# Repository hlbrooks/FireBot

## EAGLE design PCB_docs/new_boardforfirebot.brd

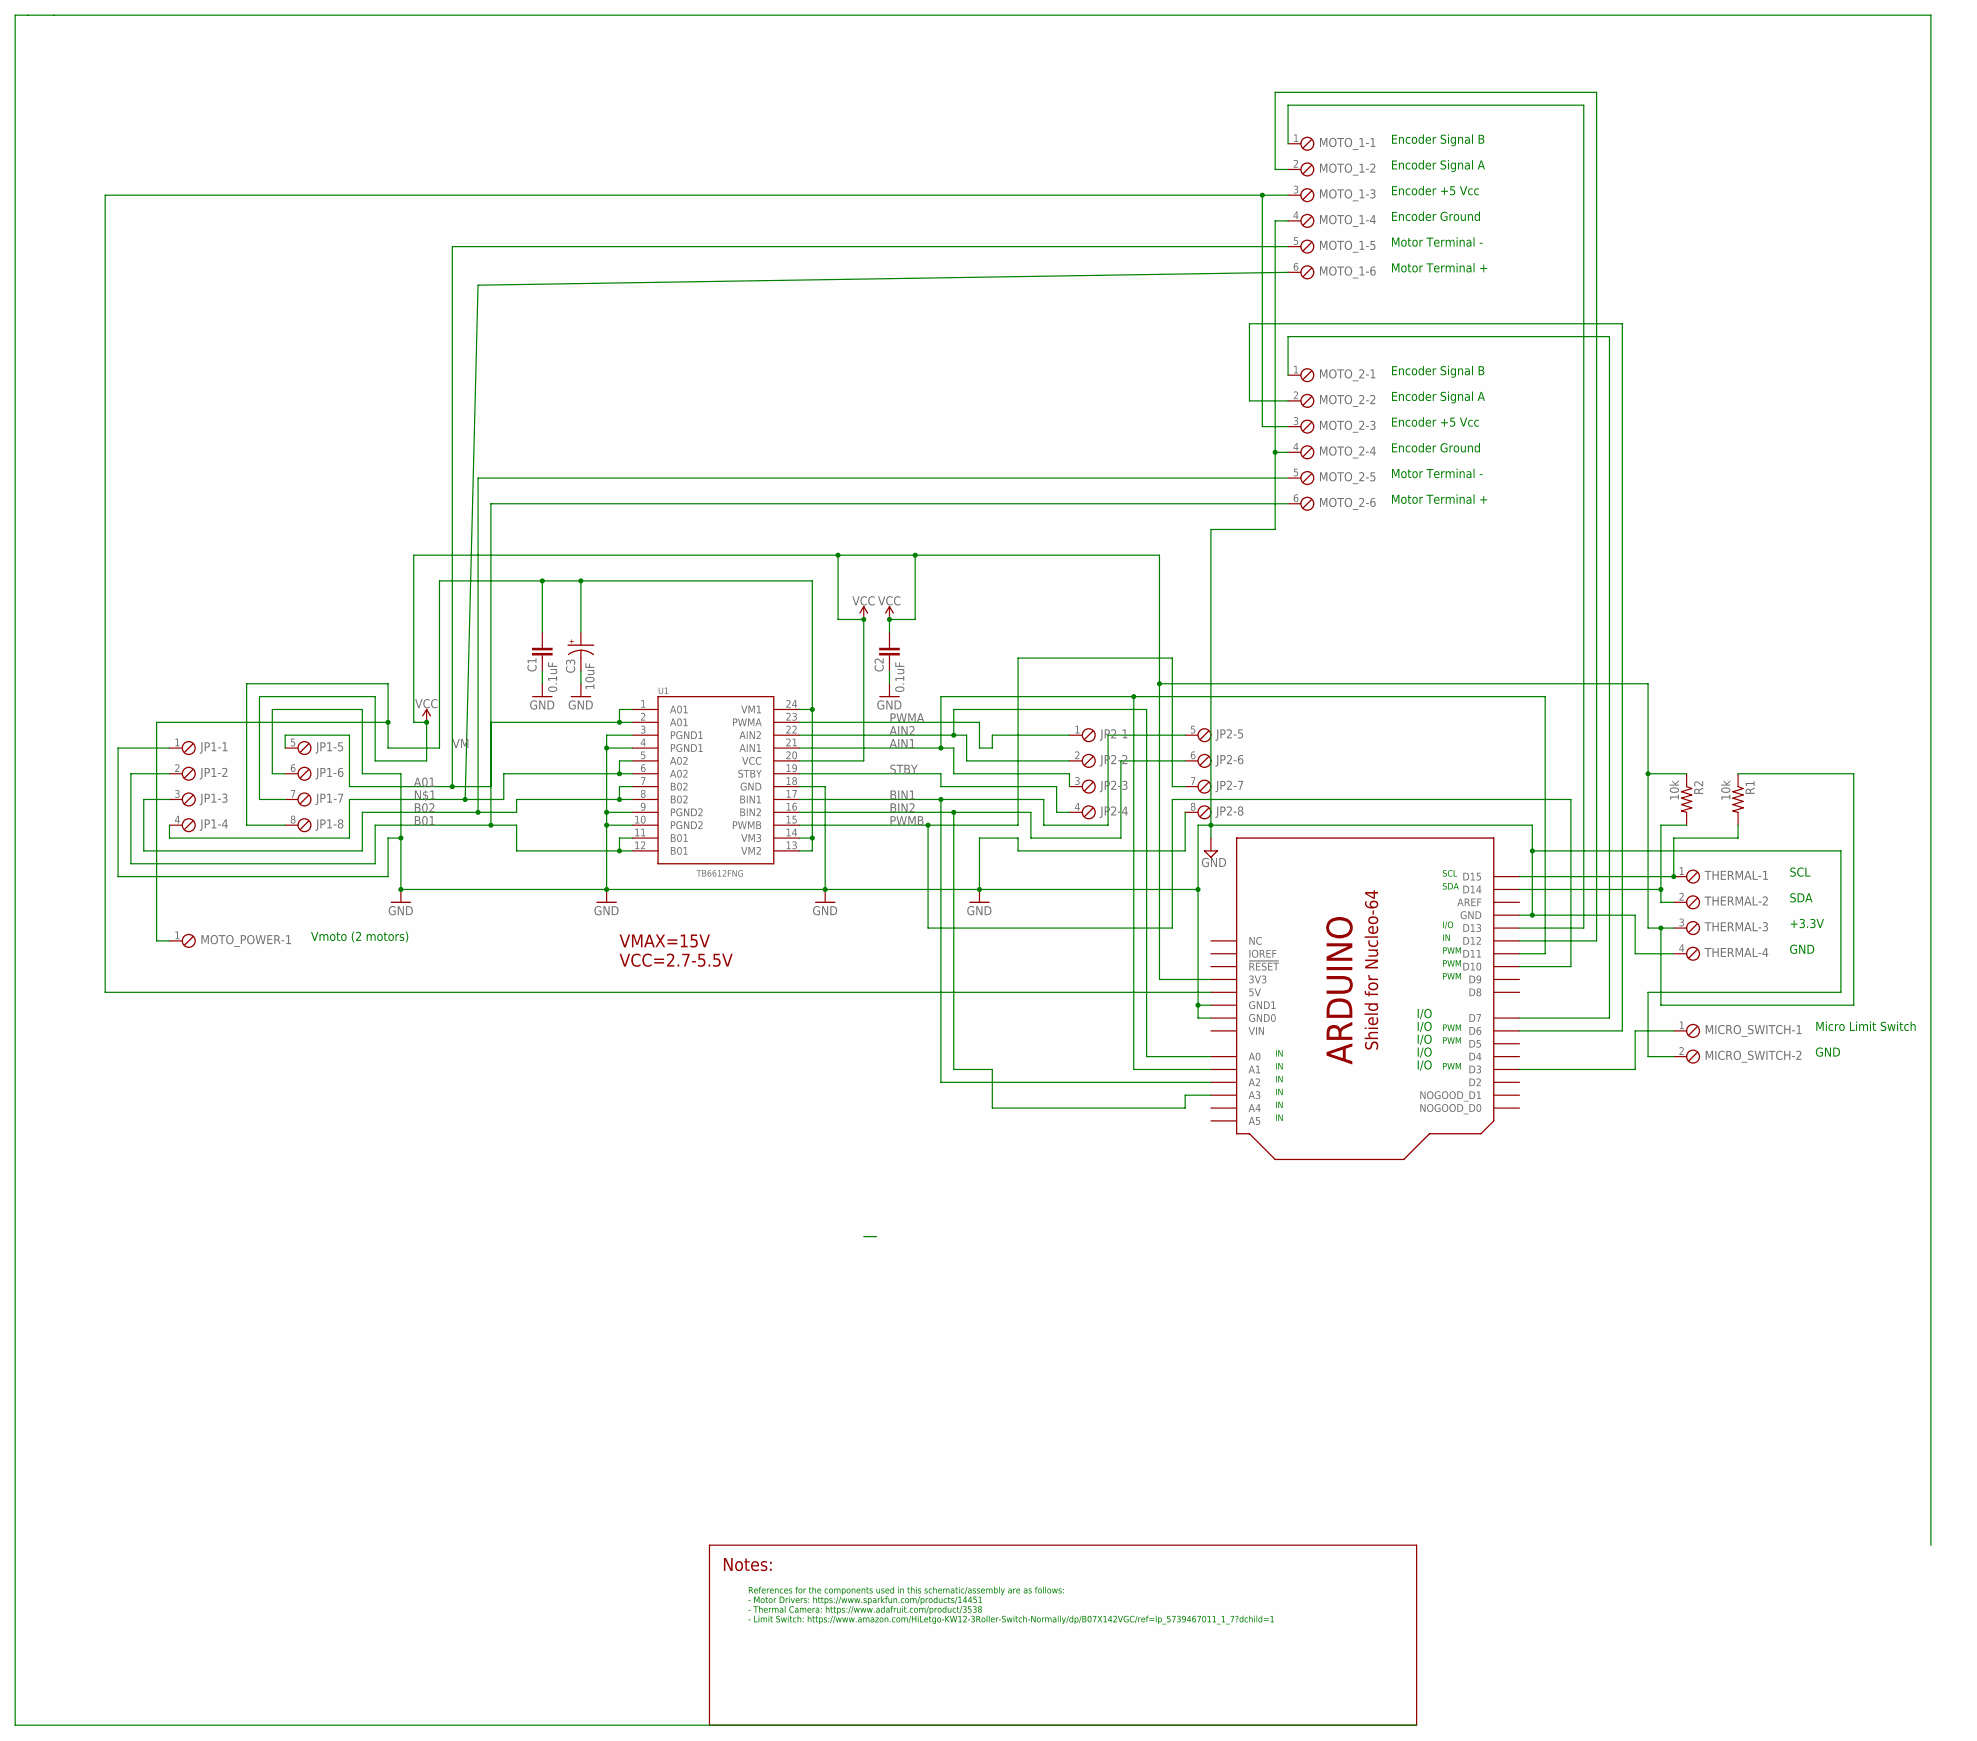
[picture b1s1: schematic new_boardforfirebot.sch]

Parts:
C1, C2: 0.1uF; 0402
C3: 10uF; EIA3528
JP1, JP2: SCREWTERM_8P_254; 8POL254
MICRO_SWITCH: SCREWTERM_2P_254; 2POL254
MOTO_1, MOTO_2: SCREWTERM_6P_254; 6POL254
MOTO_POWER: SCREWTERM_2P_254; 2POL254
R1, R2: 10k; R0805
THERMAL: SCREWTERM_4P_254; 4POL254
U1: TB6612FNG; SSOP24
U$1: SHIELD_FOR_NUCLE0_64_STANDARD; SHIELD_FOR_NUCLEO_64_STD

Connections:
A01: JP1.5, MOTO_1.5, U1.1 (A01), U1.2 (A01)
AIN1: JP2.3, U1.21 (AIN1), U$1.A1, U$1.D11
AIN2: JP2.2, U1.22 (AIN2), U$1.A0
B01: JP1.2, MOTO_2.6, U1.11 (B01), U1.12 (B01)
B02: JP1.3, MOTO_2.5, U1.7 (B02), U1.8 (B02)
BIN1: JP2.5, U1.17 (BIN1), U$1.A2
BIN2: JP2.6, U1.16 (BIN2), U$1.A3
GND: C1.2, C2.2, C3.C (-), JP1.1, JP1.6, JP2.8, MICRO_SWITCH.2, MOTO_1.4, MOTO_2.4, THERMAL.4, U1.3 (PGND1), U1.4 (PGND1), U1.9 (PGND2), U1.10 (PGND2), U1.18 (GND), U$1.GND, U$1.GND1 (GND0), U$1.GND2 (GND1)
unnamed: JP1.4, MOTO_1.6, U1.5 (A02), U1.6 (A02)
unnamed: MOTO_1.3, MOTO_2.3, U$1.5V
unnamed: MOTO_1.1, U$1.D13
unnamed: MOTO_1.2, U$1.D12
unnamed: MOTO_2.1, U$1.D7
unnamed: MOTO_2.2, U$1.D6
unnamed: R1.2, THERMAL.1, U$1.D15
unnamed: MICRO_SWITCH.1, U$1.D3
unnamed: R2.2, THERMAL.2, U$1.D14
PWMA: JP2.1, U1.23 (PWMA)
PWMB: JP2.7, U1.15 (PWMB), U$1.D10
STBY: JP2.4, U1.19 (STBY)
VCC: C2.1, JP1.7, R1.1, R2.1, THERMAL.3, U1.20 (VCC), U$1.3V (3V3)
VIN: U$1.VIN
VM: C1.1, C3.A (+), JP1.8, MOTO_POWER.1, U1.13 (VM2), U1.14 (VM3), U1.24 (VM1)

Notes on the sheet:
VMAX=15V VCC=2.7-5.5V
Encoder Signal B
Encoder Signal A
Encoder +5 Vcc
Encoder Ground
Motor Terminal -
Motor Terminal +
Vmoto (2 motors)
PWM
SCL
SDA
I/O
+3.3V
GND
Micro Limit Switch
References for the components used in this schematic/assembly are as follows: - Motor Drivers: https://www.sparkfun.com/products/14451 - Thermal Camera: https://www.adafruit.com/product/3538 - Limit Switch: https://www.amazon.com/HiLetgo-KW12-3Roller-Switch-Normally/dp/B07X142VGC/ref=lp_5739467011_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

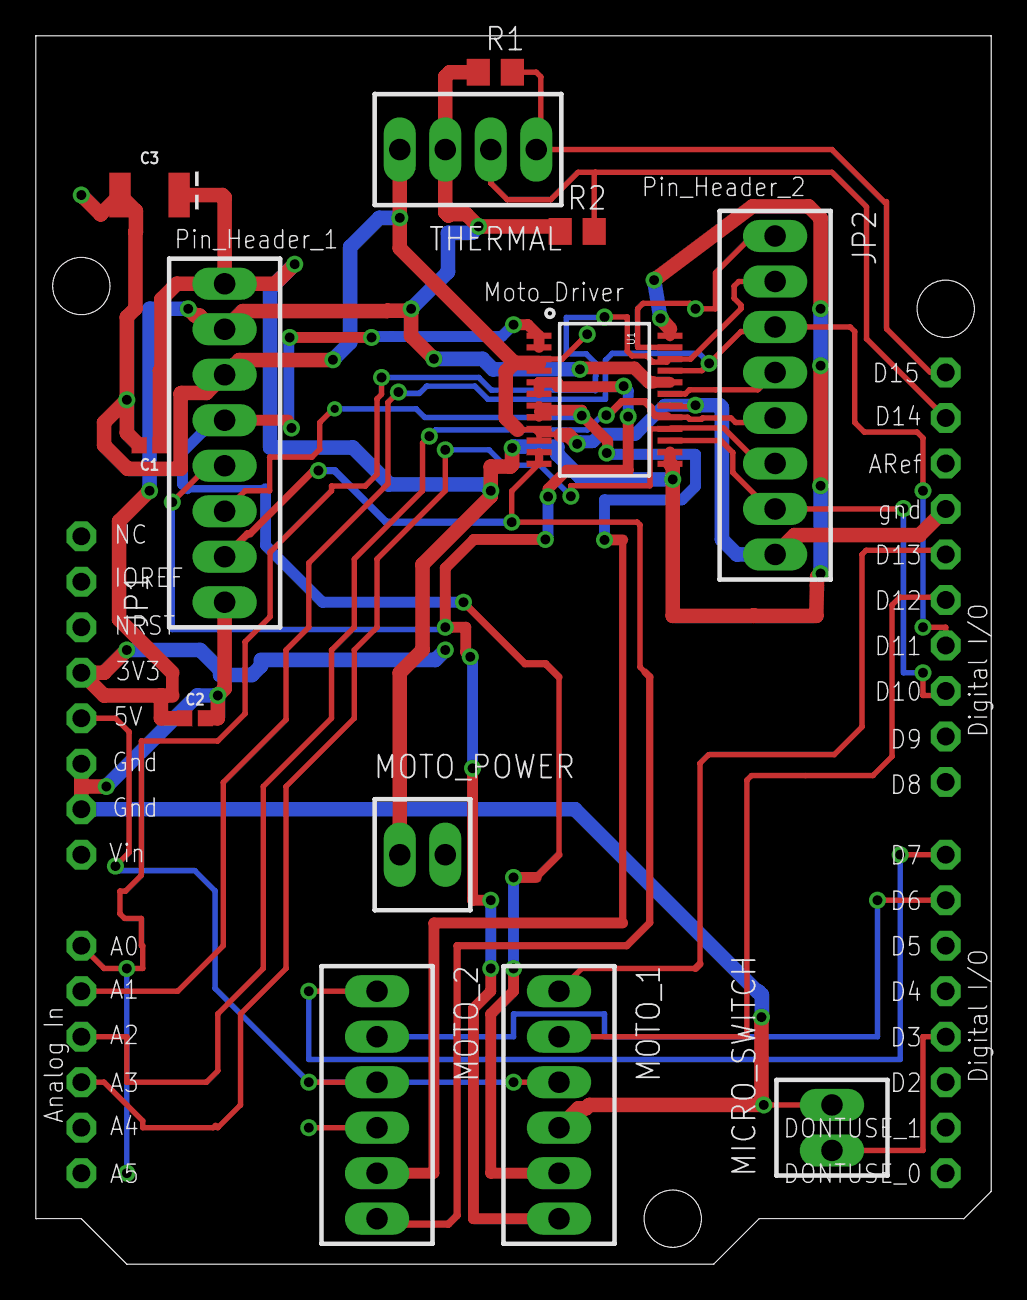
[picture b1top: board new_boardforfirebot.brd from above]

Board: 2 copper layers, 53.3 x 68.6 mm, 14 parts (0 on the bottom side), 22 nets.

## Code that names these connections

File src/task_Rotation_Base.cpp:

/** @file task_Rotation_Base.cpp
 *  This task rotates the turntable which holds the rest of the assembly while a fire has not been
 *  detected by the thermal camera.  The turntable is rotated with a high torque motor.  When a 
 *  fire is detected, this motor's rotation is halted while the fire is extinguished.  When 
 *  extinguished, the motor's rotation resumes.
 * 
 *  @author  Hunter Brooks & William Dorosk
 *  @date    20 Nov 2021 File Created
 *  @date    2  Dec 2021 Finalized file
 */

// To begin, #include the necessary libraries for this task
#include <Arduino.h>
#include <PrintStream.h>
#if (defined STM32L4xx || defined STM32F4xx)
    #include <STM32FreeRTOS.h>
#endif

#include "taskshare.h"               // Header for inter-task shared data
#include "taskqueue.h"               // Header for inter-task data queues
#include "shares.h"                  // Header for shares
#include "SparkFun_TB6612.h"         // Header for the methods provided by the motor driver manufacturer
#include "task_Rotation_Base.h"      // Header for turntable rotation task module

/// The number of RTOS ticks between runs of the turntable rotation task
const TickType_t ROTATION_BASE_PERIOD = 100;

// Define the pins that will be used to integrate the  motor driver to the Nucleo

/// One of the two inputs that determines the direction
#define AIN1 PA8  
/// One of the two inputs that determines the direction  
#define AIN2 PB10  
/// PWM input that controls the speed
#define PWMA PA7   
/// Allows the H-bridges to work when high (has a pulldown resistor so it must actively pulled high) 
#define STBY PB4    

/// This constant is used to allow motor configuration to line up with function names like "forward" within Motor class.  Value can be 1 or -1
const int offsetA = 1;

/// An object of class Motor for the motor that rotates the turntable
Motor motor1 = Motor(AIN1, AIN2, PWMA, offsetA, STBY);

/** @brief   This is the task function that controlls the rotation of the motor that turns the turntable.
 *  @details This task rotates the turntable which holds the rest of the assembly while a fire has not been
 *           detected by the thermal camera.  The turntable is rotated with a high torque motor.  When a 
 *           fire is detected, this motor's rotation is halted while the fire is extinguished.  When 
 *           extinguished, the motor's rotation resumes.
 *  @param   p_params A pointer to function parameters which we don't use.
 */

void task_Rotation_Base (void* p_params)
{
    (void)p_params;          // Shuts up a compiler warning

    // initialize each share value to zero
    fire_detected.put(0);    
    state_extinguish.put(0); 
    restart_program.put(0);
    
    // Initialise the xLastWakeTime variable with the current time.
    // It will be used to run the task at precise intervals
    TickType_t xLastWakeTime = xTaskGetTickCount();

    // Begin program with turntable rotating
    motor1.drive(250);

    for (;;)
    {
        // If a fire is not detected and if the program is not being restarted, the task will exit on each pass
        // If a fire is detected, the turntable motor will halt rotation and the share controlling the task_Extinguish
        //     FSM will be set to one
        // If the program is being restarted, the task will resume the motor rotation, and the shares will be reset to zero

        if (fire_detected.get() == 1) //share
        {
            if (state_extinguish.get() == 0) //share
            { 
                motor1.drive(0);
                state_extinguish.put(1);  //share
            }
            else 
            { 
            }
        }
        else
        {
        }
        if (restart_program.get() == 1)  //share
        {
            motor1.drive(250);
            restart_program.put(0);      //share
        }
        else
        {
        }
        // This type of delay waits until it has been the given number of RTOS
        // ticks since the task previously began running. This prevents timing
        // inaccuracy due to not accounting for how long the task took to run
        vTaskDelayUntil (&xLastWakeTime, ROTATION_BASE_PERIOD);
    }
}

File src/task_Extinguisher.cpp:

/** @file task_Extinguisher.cpp
 *  This task consists of an FSM which extinguishes a fire when one is detected.
 *  When a fire is detected, this task actuates a motor that is press-fit to a 
 *  lead screw which clamps down the lever of a fire extinguisher that is mounted
 *  to the assembly.  When the lever has been fully compressed, a micro limit 
 *  switch is pressed which switches the direction of the motor.  The motor rotates 
 *  the lead screw thus translating the motor until a second mircro limit switch 
 *  is pressed.  At this point, the motor stops rotating, and the assembly is reset,
 *  thus ready to extinguish another fire. The motor which rotates the turntable 
 *  resumes rotation.
 * 
 *  @author  Hunter Brooks & William Dorosk
 *  @date    20 Nov 2021 File Created
 *  @date    2  Dec 2021 Finalized file
 */

// To begin, #include the necessary libraries for this task
#include <Arduino.h>
#include <PrintStream.h>
#if (defined STM32L4xx || defined STM32F4xx)
    #include <STM32FreeRTOS.h>
#endif

#include "taskshare.h"               // Header for inter-task shared data
#include "taskqueue.h"               // Header for inter-task data queues 
#include "shares.h"                  // Header for shares
#include "SparkFun_TB6612.h"         // Header for the methods provided by the motor driver manufacturer
#include "task_Rotation_Base.h"      // Header for extinguisher task module

/// The number of RTOS ticks between runs of the extinguisher task
const TickType_t Extinguisher_PERIOD = 100;

// Define the pins that will be used to integrate the  motor driver to the Nucleo

/// One of the two inputs that determines the direction
#define BIN1 PB5
/// One of the two inputs that determines the direction
#define BIN2 PA10  
/// PWM input that controls the speed 
#define PWMB PB3  
/// Allows the H-bridges to work when high (has a pulldown resistor so it must actively pulled high)  
#define STBY PB4    

/// This constant is used to allow motor configuration to line up with function names like "forward" within Motor class.  Value can be 1 or -1
const int offsetB = 1;

/// An object of class Motor for the motor that actuates the fire extinguisher
Motor motor2 = Motor(BIN1, BIN2, PWMB, offsetB, STBY);

/** @brief   This is the task function that actuates the fire extinguisher to extinguish the detected fire
 *  @details This task consists of an FSM which extinguishes a fire when one is detected. When a fire is 
 *           detected, this task actuates a motor that is press-fit to a lead screw which clamps down the
 *           lever of a fire extinguisher that is mounted to the assembly.  When the lever has been fully
 *           compressed, a micro limit switch is pressed which switches the direction of the motor.  The 
 *           motor rotates the lead screw thus translating the motor until a second mircro limit switch 
 *           is pressed.  At this point, the motor stops rotating, and the assembly is reset, thus ready to
 *           extinguish another fire. The motor which rotates the turntable resumes rotation.
 *  @param   p_params A pointer to function parameters which we don't use.
 */

void task_Extinguisher (void* p_params)
{
    (void)p_params;                             // Shuts up a compiler warning
    
    // initialize each local variable value to zero
    uint8_t start_extinguish = 0;    // variable that determines if the motor has started moving toward extinguisher
    uint8_t start_unclamp = 0;       // variable that determines if the motor has reversed direction from extinguisher

    // Initialise the xLastWakeTime variable with the current time.
    // It will be used to run the task at precise intervals
    TickType_t xLastWakeTime = xTaskGetTickCount();

    for (;;)
    {
        // What follows is an FSM for the extinguish operation.  The function of each state is as follows:
        //     (1) - Begin motor rotation toward extinguisher
        //     (2) - Reverse motor rotation direction after the extinguisher lever has been fully compressed
        //     (3) - Halt motor rotation, set restart_program share value to one that notifies turntable rotation task to resume
        //           rotation and reset the share values to zero
        //     (0) - Intermediate state where the task sits until another fire is detected          

        if (state_extinguish.get() == 1)  //share
        {
            if (start_extinguish == 0) 
            {
                motor2.drive(250);
                start_extinguish = 1; 
            }
            else
            {
            }
        }
        else if (state_extinguish.get() == 2)  //share
        {
            if (start_unclamp == 0)
            {
                motor2.drive(-250);
                start_unclamp = 1;
            }
            else
            {
            }
        }     
        else if (state_extinguish.get() == 3)  //share
        {
            motor2.drive(0);           
            start_extinguish = 0; //
            start_unclamp = 0;
            restart_program.put(1);  //share
            state_extinguish.put(0);  //share
            fire_detected.put(0);
        }
        else
        {
        }
        // This type of delay waits until it has been the given number of RTOS
        // ticks since the task previously began running. This prevents timing
        // inaccuracy due to not accounting for how long the task took to run
        vTaskDelayUntil (&xLastWakeTime, Extinguisher_PERIOD);
    }
}

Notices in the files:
parts and their libraries:
SparkFun-Capacitors: Licensing: Creative Commons ShareAlike 4.0 International - https://creativecommons.org/licenses/by-sa/4.0
